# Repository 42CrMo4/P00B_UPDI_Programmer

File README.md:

# UPDI Programmer

A UPDI Programmer to use the Würth Redfit Skedd Connector and a switch for UPDI and TX of the MCU.

### Goal & Status

Goal: Prototype
Status: implementation

#### Definitions
| undefined                             | learn                                                                                            | prototype                  | 80-20-rule                                                   | polished Product |
|---------------------------------------|--------------------------------------------------------------------------------------------------|----------------------------|--------------------------------------------------------------|------------------|
| not known what the project will bring | personally learn something new (function, design, process) otherwise no usefull outcome expected | a working prototype or mvp | 80% outcome with 20% effort. Dont expect a finished product. | -                |

| idea                   | design                                                | implementation | testing | finished |
|------------------------|-------------------------------------------------------|----------------|---------|----------|
| brainstorming workflow | putting together a goal list, architecture, hig level | schematic, pcb |         |          |

## Todo

## Description. 

| Font                                                                    | Back                                                                      |
|-------------------------------------------------------------------------|---------------------------------------------------------------------------|
|  |  |

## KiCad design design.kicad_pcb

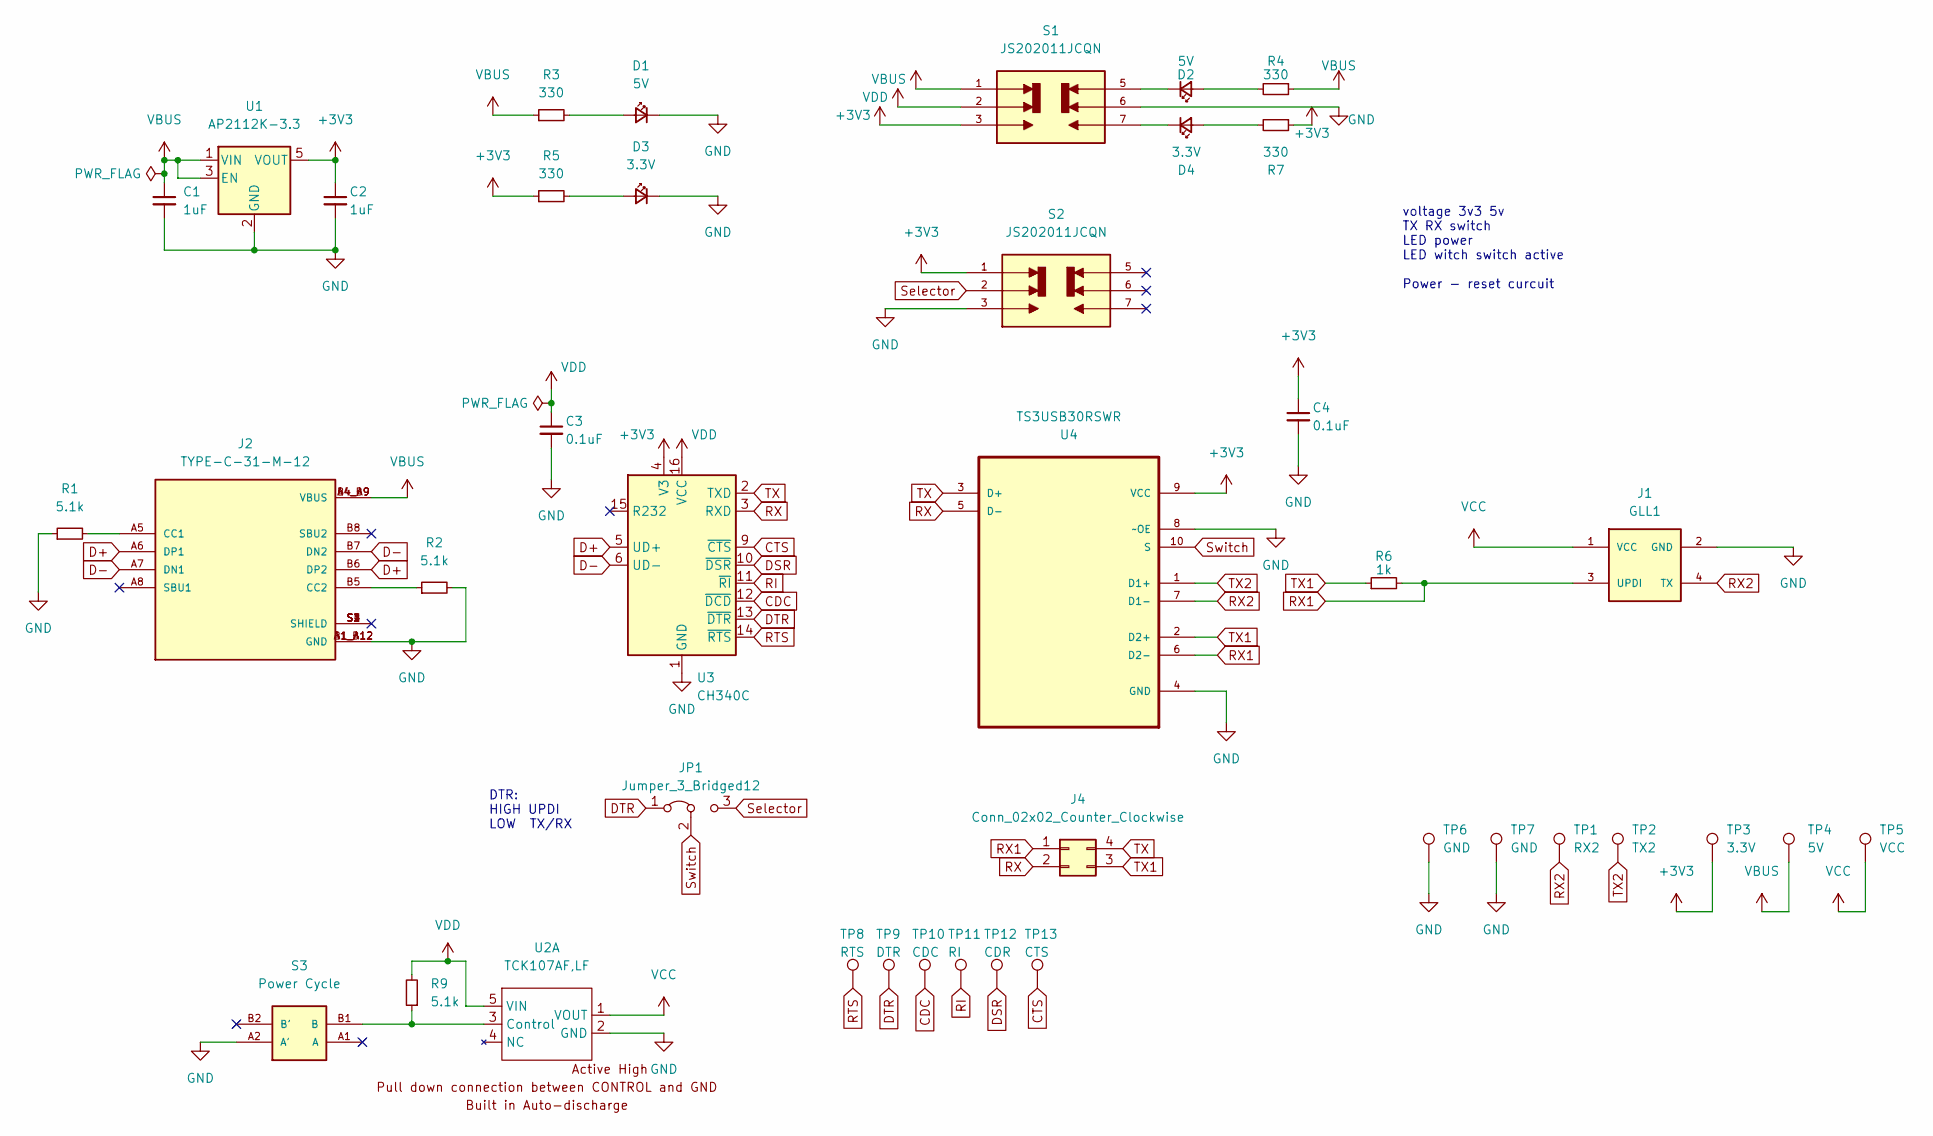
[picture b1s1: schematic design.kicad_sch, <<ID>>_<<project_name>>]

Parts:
C1, C2: 1uF; C_0805_2012Metric
C3, C4: 0.1uF; C_0805_2012Metric
D1, D2: 5V; LED_0805_2012Metric
D3, D4: 3.3V; LED_0805_2012Metric
J1: GLL1
J2: TYPE-C-31-M-12; TYPE-C-31-M-12_HRO_TYPE-C-31-M-12; PARTREV 2020.12.08
J4: Conn_02x02_Counter_Clockwise; PinHeader_2x02_P2.54mm_Vertical
JP1: Jumper_3_Bridged12; SolderJumper-3_P1.3mm_Bridged12_Pad1.0x1.5mm_NumberLabels
R1, R2, R9: 5.1k; R_0805_2012Metric
R3, R4, R5, R7: 330; R_0805_2012Metric
R6: 1k; R_0805_2012Metric
S1, S2: JS202011JCQN; SW_JS202011JCQN; PARTREV 11 Nov 19
S3: Power Cycle; EVP-BFAC1A000_EVPBFAC1A000; MOUSER_PART_NUMBER 667-EVP-BFAC1A000
TP1: RX2; TestPoint_Pad_D2.0mm
TP2: TX2; TestPoint_Pad_D2.0mm
TP3: 3.3V; TestPoint_Pad_D2.0mm
TP4: 5V; TestPoint_Pad_D2.0mm
TP5: VCC; TestPoint_Pad_D2.0mm
TP6, TP7: GND; TestPoint_Pad_D1.0mm
TP8: RTS; TestPoint_Pad_D1.0mm
TP9: DTR; TestPoint_Pad_D1.0mm
TP10: CDC; TestPoint_Pad_D1.0mm
TP11: RI; TestPoint_Pad_D1.0mm
TP12: CDR; TestPoint_Pad_D1.0mm
TP13: CTS; TestPoint_Pad_D1.0mm
U1: AP2112K-3.3; SOT-23-5
U2: TCK107AF,LF; SOT-23-5
U3: CH340C; SOIC-16_3.9x9.9mm_P1.27mm
U4: TS3USB30RSWR; TS3USB30RSWR_QFN40P140X180X55-10N; MPN TS3USB30RSWR

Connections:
+3V3: C2.1, C4.1, R5.1, R7.1, S1.3, S2.1, TP3.1, U1.5 (VOUT), U3.4 (V3), U4.9 (VCC)
CDC: TP10.1, U3.12 (~DCD)
CTS: TP13.1, U3.9 (~CTS)
D+: J2.A6 (DP1), J2.B6 (DP2), U3.5 (UD+)
D-: J2.A7 (DN1), J2.B7 (DN2), U3.6 (UD-)
DSR: TP12.1, U3.10 (~DSR)
DTR: JP1.1 (A), TP9.1, U3.13 (~DTR)
GND: C1.2, C2.2, C3.2, C4.2, D1.1 (K), D3.1 (K), J1.2 (GND), J2.A1_B12 (GND), J2.B1_A12 (GND), R1.1, R2.2, S1.6, S2.3, S3.A2 (A'), TP6.1, TP7.1, U1.2 (GND), U2.2 (GND), U3.1 (GND), U4.4 (GND), U4.8 (~OE)
unnamed: D1.2 (A), R3.2
unnamed: D2.1 (K), S1.5
unnamed: D2.2 (A), R4.2
unnamed: D3.2 (A), R5.2
unnamed: D4.1 (K), S1.7
unnamed: D4.2 (A), R7.2
unnamed: J2.A5 (CC1), R1.2
unnamed: J2.B5 (CC2), R2.1
unnamed: R9.1, S3.B1 (B), U2.3 (Control)
RI: TP11.1, U3.11 (~RI)
RTS: TP8.1, U3.14 (~RTS)
RX: J4.2, U3.3 (RXD), U4.5 (D-)
RX1: J1.3 (UPDI), J4.1, R6.2, U4.6 (D2-)
RX2: J1.4 (TX), TP1.1, U4.7 (D1-)
Selector: JP1.3 (B), S2.2
Switch: JP1.2 (C), U4.10 (S)
TX: J4.4, U3.2 (TXD), U4.3 (D+)
TX1: J4.3, R6.1, U4.2 (D2+)
TX2: TP2.1, U4.1 (D1+)
VBUS: C1.1, J2.A4_B9 (VBUS), J2.B4_A9 (VBUS), R3.1, R4.1, S1.1, TP4.1, U1.1 (VIN), U1.3 (EN)
VCC: J1.1 (VCC), TP5.1, U2.1 (VOUT)
VDD: C3.1, R9.2, S1.2, U2.5 (VIN), U3.16 (VCC)

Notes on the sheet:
DTR: HIGH UPDI LOW TX/RX
voltage 3v3 5v TX RX switch LED power LED witch switch active Power - reset curcuit

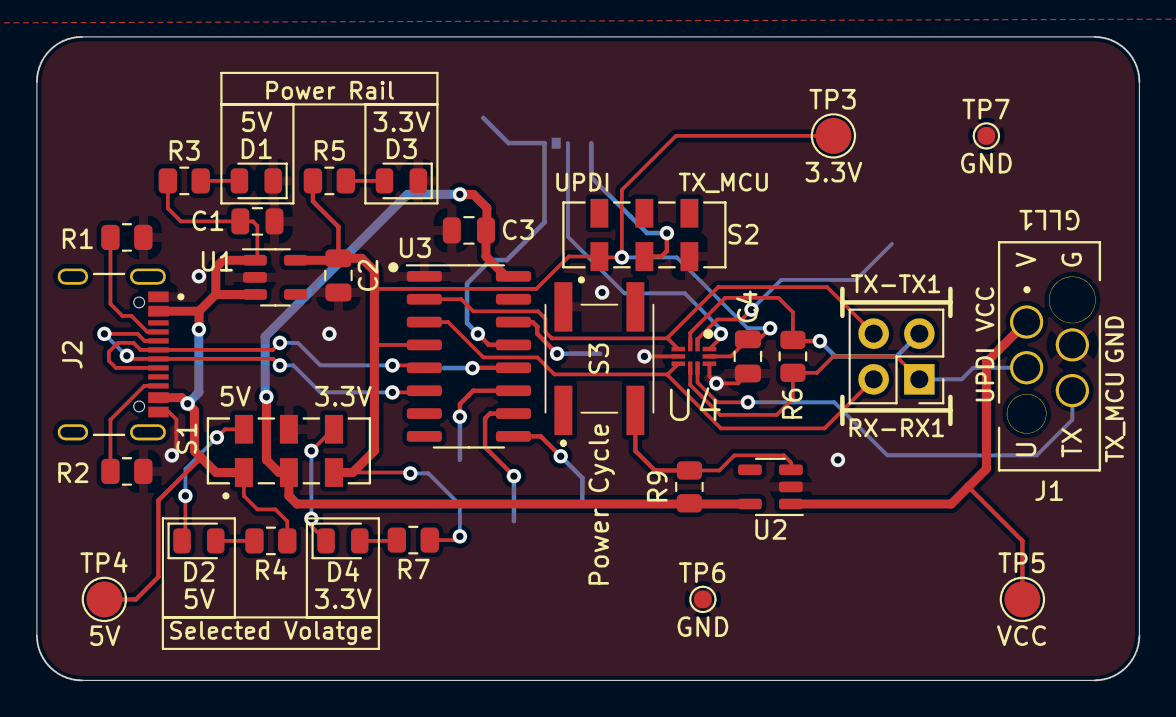
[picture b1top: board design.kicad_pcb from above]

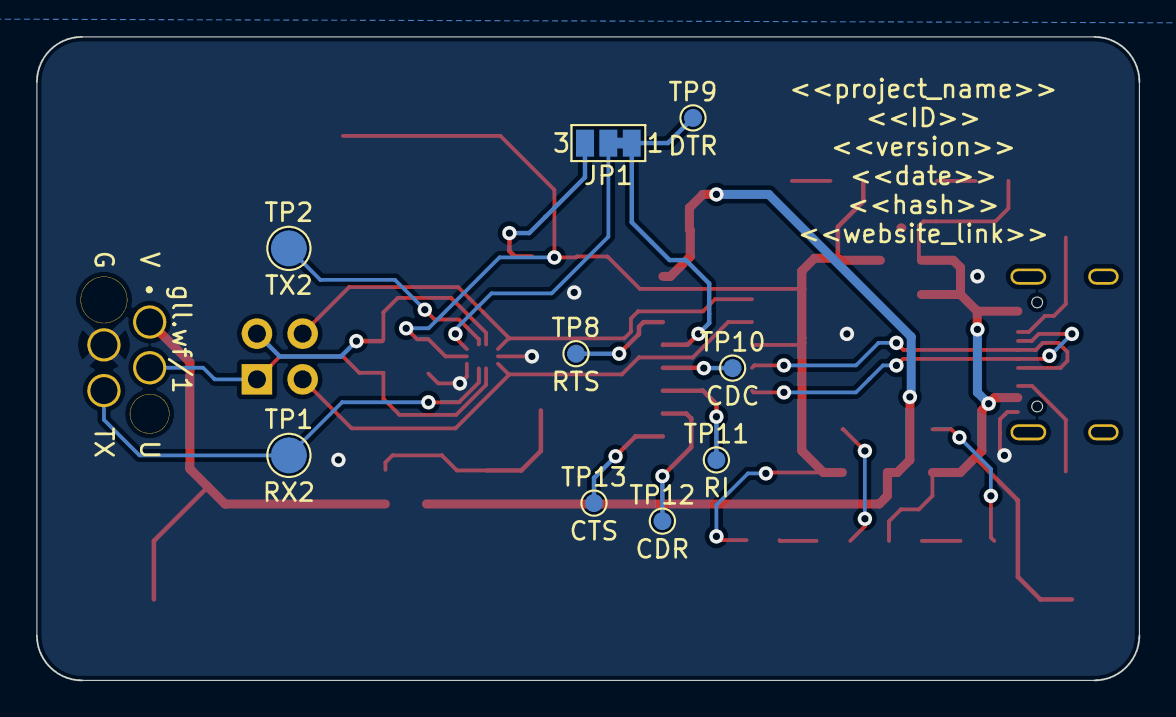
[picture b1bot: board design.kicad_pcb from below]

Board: 2 copper layers, 61.2 x 35.8 mm, 40 parts (9 on the bottom side), 30 nets.

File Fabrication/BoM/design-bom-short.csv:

Row,Description,Part,References,Value,Footprint,Quantity Per PCB,Status,Datasheet,MF,MAXIMUM_PACKAGE_HEIGHT,Package,Price,Check_prices,STANDARD,PARTREV,SnapEDA_Link,MP,Purchase-URL,Availability,MANUFACTURER,MANUFACTURER_NAME,MOUSER_PRICE-STOCK,ALLIED_NUMBER,RS_PART_NUMBER,ALLIED_PRICE-STOCK,MOUSER_PART_NUMBER,HEIGHT,RS_PRICE-STOCK,MANUFACTURER_PART_NUMBER,SNAPEDA_PN,IPN,MPN,OC_FARNELL,SUPPLIER,OC_NEWARK
1,"Unpolarized capacitor, small symbol",C_Small,C3 C4,0.1uF,C_0805_2012Metric,2, ,~,,,,,,,,,,,,,,,,,,,,,,,,,,,
2,"Unpolarized capacitor, small symbol",C_Small,C1 C2,1uF,C_0805_2012Metric,2, ,~,,,,,,,,,,,,,,,,,,,,,,,,,,,
3,"Light emitting diode, small symbol",LED_Small,D3 D4,3.3V,LED_0805_2012Metric,2, ,~,,,,,,,,,,,,,,,,,,,,,,,,,,,
4,"Light emitting diode, small symbol",LED_Small,D1 D2,5V,LED_0805_2012Metric,2, ,~,,,,,,,,,,,,,,,,,,,,,,,,,,,
5,"4 Position Ribbon Cable Connector Black IDC 28 AWG Through Hole, SKEDD",490107670412,J1,490107670412,490107670412_WURTH_490107670412,1, ,,Wurth Elektronik,10.45 mm,None,None,https://www.snapeda.com/parts/490107670412/Wurth+Elektronik/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,Manufacturer Recommendations,002.003,https://www.snapeda.com/parts/490107670412/Wurth+Elektronik/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,490107670412,https://www.snapeda.com/api/url_track_click_mouser/?unipart_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 Elektronik&part_name=490107670412&search_term=skedd,In Stock,Wuerth Elektronik,,,,,,,,,,,,,,,
6,"Generic connector, double row, 02x02, counter clockwise pin numbering scheme (similar to DIP package numbering), script generated (kicad-library-utils/schlib/autogen/connector/)",Conn_02x02_Counter_Clockwise,J4,Conn_02x02_Counter_Clockwise,PinHeader_2x02_P2.54mm_Vertical,1, ,~,,,,,,,,,,,,,,,,,,,,,,,,,,,
7,USB Connectors 24 Receptacle 1 8.94*7.3mm RoHS,TYPE-C-31-M-12,J2,TYPE-C-31-M-12,TYPE-C-31-M-12_HRO_TYPE-C-31-M-12,1, ,,"HRO Electronics Co., Ltd.",3.26 mm,Package,None,https://www.snapeda.com/parts/TYPE-C-31-M-12/HRO+Electronics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,Manufacturer Recommendations,2020.12.08,https://www.snapeda.com/parts/TYPE-C-31-M-12/HRO+Electronics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,TYPE-C-31-M-12,,Not in stock,"HRO Electronics Co., Ltd.",,,,,,,,,,TYPE-C-31-M-12,,,,,
8,"Jumper, 3-pole, pins 1+2 closed/bridged",Jumper_3_Bridged12,JP1,Jumper_3_Bridged12,SolderJumper-3_P1.3mm_Bridged12_Pad1.0x1.5mm_NumberLabels,1, ,~,,,,,,,,,,,,,,,,,,,,,,,,,,,
9,"Resistor, small symbol",R_Small,R3 R4 R5 R7,330,R_0805_2012Metric,4, ,~,,,,,,,,,,,,,,,,,,,,,,,,,,,
10,"Resistor, small symbol",R_Small,R6,1k,R_0805_2012Metric,1, ,~,,,,,,,,,,,,,,,,,,,,,,,,,,,
11,"Resistor, small symbol",R_Small,R1 R2 R9,5.1k,R_0805_2012Metric,3, ,~,,,,,,,,,,,,,,,,,,,,,,,,,,,
12,Slide Switch DPDT Surface Mount,JS202011JCQN,S1 S2,JS202011JCQN,SW_JS202011JCQN,2, ,,C&K,5.6 mm,DPDT-6 C&amp;K,None,https://www.snapeda.com/parts/JS202011JCQN/C%2526K/view-part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,Manufacturer Recommendations,11 Nov 19,https://www.snapeda.com/parts/JS202011JCQN/C%2526K/view-part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,JS202011JCQN,,In Stock,C&K,,,,,,,,,,,,,,,
13,Tactile Switches 6.0x6.0x3.4mm 2N w/4 Term .25mm Trvl IP67 Panasonic 0.25mm travel with 4 Terminal | Panasonic Electronic Components EVP-BFAC1A000,EVP-BFAC1A000,S3,Power Cycle,EVP-BFAC1A000_EVPBFAC1A000,1, ,,Panasonic Electronic,,None,None,https://www.snapeda.com/parts/EVP-BFAC1A000/Panasonic+Electr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,,,https://www.snapeda.com/parts/EVP-BFAC1A000/Panasonic+Electr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,EVP-BFAC1A000,https://www.snapeda.com/api/url_track_click_mouser/?unipart_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 Electronic&part_name=EVP-BFAC1A000&search_term=evp-bfac1a000,In Stock,,Panasonic,https://www.mouser.com/Search/Refine.aspx?Keyword=667-EVP-BFAC1A000,70900260,,https://www.alliedelec.com/panasonic-evp-bfac1a000/70900260/,667-EVP-BFAC1A000,3.7mm,,EVP-BFAC1A000,,,,,,
14,"600mA low dropout linear regulator, with enable pin, 3.8V-6V input voltage range, 3.3V fixed positive output, SOT-23-5",AP2112K-3.3,U1,AP2112K-3.3,SOT-23-5,1, ,https://www.diodes.com/assets/Datasheets/AP2112.pdf,,,,,,,,,,,,,,,,,,,,,,,,,,,
15,"USB serial converter, UART, SOIC-16",CH340C,U3,CH340C,SOIC-16_3.9x9.9mm_P1.27mm,1, ,https://datasheet.lcsc.com/szlcsc/Jiangsu-Qin-Heng-CH340C_C8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,,,,,,,,,,,,,,,,,,,,,,,ICS-0251,,,,
16,,"TCK107AF,LF",U2,"TCK107AF,LF",SOT-23-5,1, ,https://toshiba.semicon-storage.com/info/TCK108AF_datasheet_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,,,,,,,,,,,,,,,,,,,,,,,,,,,
17,High-speed USB 2.0 (480-Mbps) 1:2 multiplexer & demultiplexer switch with single enable,TS3USB30RSWR,U4,TS3USB30RSWR,TS3USB30RSWR_QFN40P140X180X55-10N,1, ,,Texas Instruments,,UQFN-10 UQFN-10 Texas Instruments,None,https://www.snapeda.com/parts/TS3USB30RSWR/Texas+Instruments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,,,https://www.snapeda.com/parts/TS3USB30RSWR/Texas+Instruments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,TS3USB30RSWR,https://www.snapeda.com/api/url_track_click_mouser/?unipart_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 Instruments&part_name=TS3USB30RSWR&search_term=ts3usb30,In Stock,,,,,,,,,,,,,TS3USB30RSWR,1755574,Texas Instruments,45P8339

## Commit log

2024-02-18 update actions to new version
2024-02-18 update actions
2024-02-19 external WF
2024-02-19 use only external WF for BOM
2024-02-19 action v0.47
2024-02-19 update all to external WF
2024-02-19 use external Workflow Repo
2024-02-20 play around
2024-02-20 add steps
2024-02-23 add components
2024-03-02 cleanup
2024-03-02 small changes
2024-03-02 update for logo
2024-03-02 remove logo
2024-03-02 Kibot show IPN in iBOM
2024-03-02 add IPN
2024-03-03 add release docs
2024-03-03 Update Bom and PCB_top
2024-03-03 Archive & Renew release docs
2024-03-03 readme for v1.0
2024-04-14 use v6.0 tag
2025-03-24 correct power cycle switch pins
    internally connected pins where used instead of switched pins.
2025-03-24 correct serialUPDI resistor
    the correct way is in the TX line
    add picture of serialUPDI wiring
2025-03-24 PCB fix serialUPDI resistor and power switch pins
2025-03-25 Add DTR automatic switching and Testpoints
2025-03-25 change silkscreen
2025-03-25 use v1.0 as Diff old reference
2025-03-25 update PCB Diff
    all layers and unfill zones
2025-03-25 change zoom lavel 3d render
2025-03-25 make change TX1/RX1 and TX2/RX2 more visible in DIFF output
2025-04-04 Update footprint from Library - Stencil Data
    Tabs of the Type-C connector had no solder paste and are prone to disconnect.
2025-04-04 Add Pin1 marker
    CH340C
    TS3USB30RSWR
2025-04-04 Breaking: Update to GLL1 connector standard
    gll.wf/1
    Pinout changed for J1
2025-04-04 exclude unneeded switch from BOM
    As long the automatic switchover works this switch is not needed and without cutting JP1 it has no affect.
2025-04-04 Typo in path of 3D model
2025-04-04 refactor vias and silkscreen
2025-04-04 make each shield pin of type-c unique
    to get rid of DRC errors
2025-04-04 refactor 3 point interconnect in schematic
2025-04-05 keep Signal voltage for TS3USB below max.
    I/O signals are at 3.3V and do not withstand 5V
